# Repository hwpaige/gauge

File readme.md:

# CHT Gauge

A twin cylinder head temperature (CHT) gauge running on a Banana Pi M4 Zero, displayed on a 1.3" round SPI LCD. Designed to look like a dark-themed aircraft avionics instrument — two filled-arc gauges side by side, one per cylinder, with colour-coded temperature zones and a D-DIN digital readout.

---

## Hardware

| Component | Part |
|---|---|
| SBC | Banana Pi M4 Zero (Allwinner H618, quad-core A53) |
| Display | Pimoroni 1.3" Round SPI Colour LCD (ST7789, 240×240) — PIM570 |
| Thermocouple | MAX31855 or MAX6675 breakout (×2, one per cylinder) |
| OS | Armbian Debian Trixie Minimal |

**Important**: The kernel must provide `/dev/fb0` for the ST7789 (see "Kernel framebuffer driver" below). The Python app no longer drives the display directly.

---

## Wiring

### Display → BPI M4 Zero 40-pin header

The kernel framebuffer overlay (not the Python app) owns the pins. Example mapping used by current overlays/driver code (confirm against your .dts):

| Display Pin | Signal          | BPI Header Pin | Notes (Allwinner)     |
|-------------|-----------------|----------------|-----------------------|
| VCC         | 3.3V            | Pin 1          |                       |
| GND         | GND             | Pin 6          |                       |
| CS          | SPI1 CS0 (PH5)  | Pin 24         |                       |
| SCK         | SPI1 SCLK (PH6) | Pin 23         |                       |
| MOSI        | SPI1 MOSI (PH7) | Pin 19         |                       |
| DC          | PI16            | Pin 18         | (offset 272)          |
| RST         | PC2             | Pin 22         | (offset 66)           |
| (BL)        | (backlight)     | (Pin 35)       | Tie to 3.3V (Pin 1) if not software-controlled |

> Backlight: tie BL directly to 3.3V for always-on (recommended for gauge). The kernel panel driver typically handles reset/DC in its DT.

### Thermocouple (MAX31855 / MAX6675) — to be wired

Thermocouples share the SPI bus with the display using separate CS pins. Wiring and sensor code will be added in a future update.

---

## Project Structure

```
cht-gauge/
├── setup.sh          # One-shot bootstrap — run on fresh Armbian flash
├── gauge.py          # Main application (uses kernel /dev/fb0)
├── run.sh            # Launch script
├── test_display.py   # Legacy userspace test (may fail once kernel owns display)
├── pin_test.py       # Dev tool for probing GPIOs/SPI (kernel pins will be busy)
├── driver.py         # Legacy userspace ST7789 driver (kept for reference)
├── .gitignore
└── fonts/
    └── README.md     # Fonts are downloaded by setup.sh, not committed to repo
```

---

## Fresh Install Instructions

### 1. Flash Armbian

Download **Armbian Debian Trixie Minimal** for BPI M4 Zero:
```
https://dl.armbian.com/bananapim4zero/Trixie_current_minimal
```

Flash with [Armbian Imager](https://imager.armbian.com) or Balena Etcher. Pre-configure WiFi credentials in the imager before flashing.

### 2. SSH in

Find the device IP via your router's DHCP client list, then:

```bash
ssh root@<ip-address>
# Default password: 1234 (you'll be prompted to change it)
```

### 3. Run setup

```bash
wget https://raw.githubusercontent.com/hwpaige/gauge/master/setup.sh
bash setup.sh
```

The script will:
- Set the hostname to `moto` (SSH via `root@moto.local` after reboot)
- Enable SPI in `/boot/armbianEnv.txt`
- Install all system and Python dependencies
- Clone this repo to `/root/gauge`
- Download the D-DIN font
- Create a Python virtual environment and install packages
- Prompt to reboot

After reboot, SSH back in with:

```bash
ssh root@moto.local
```

### 4. Test the display

Once the kernel framebuffer driver is active (see below), the display is the system primary framebuffer. A basic test that the fb is working:

```bash
cat /dev/urandom > /dev/fb0   # noise on screen; Ctrl-C to stop
```

Or (inside venv):

```bash
cd /root/gauge
source venv/bin/activate
python3 -c "
import pygame, os
os.environ['SDL_VIDEODRIVER']='fbcon'; os.environ['SDL_FBDEV']='/dev/fb0'
pygame.init()
s = pygame.display.set_mode((240,280))
s.fill((255,0,0)); pygame.display.flip()
input('red fb - press enter'); pygame.quit()
"
```

(If the legacy `test_display.py` using the Python `st7789` package fails with EBUSY, that is expected once the kernel driver owns the pins — it is no longer needed.)

See "Kernel framebuffer driver" section for how the display becomes `/dev/fb0`.

### 5. Run the gauge

```bash
/root/gauge/run.sh
```

(Or manually: `cd /root/gauge && source venv/bin/activate && python3 gauge.py`)

**Important:** Because the kernel is now driving the round display as the primary framebuffer/console, you must run the gauge while on the **actual Linux console** that the display is attached to (not over SSH in most cases).

- Easiest for testing: Plug a USB keyboard into the Banana Pi. The round display should be showing the login prompt. Login directly there as root and run the command on that console.
- SSH sessions often produce `pygame.error: fbcon not available` because the SDL fbcon driver needs a real virtual terminal context.
- For production (recommended): use the included `gauge.service` so it starts automatically on boot and takes over the round display console. No keyboard or SSH run needed after setup.

### Auto-start via systemd (recommended)

From SSH on the Pi:

```bash
cd /root/gauge
git pull   # get the latest gauge.service if you haven't already

sudo cp gauge.service /etc/systemd/system/
sudo systemctl daemon-reload
sudo systemctl enable --now gauge.service

# Optional: stop the default getty so the gauge owns the console cleanly
# (the service tries to chvt to tty1)
sudo systemctl stop getty@tty1.service
sudo systemctl disable getty@tty1.service
```

Check status:

```bash
systemctl status gauge.service
journalctl -u gauge.service -f
```

To stop it temporarily and get a console back:

```bash
sudo systemctl stop gauge.service
sudo chvt 1
# or reboot
```

The service is configured to restart on failure and attaches to the framebuffer console.

See the on-screen error message in the new gauge.py for more details and a quick kernel-fb test command that *does* work over SSH.

---

## Application

`gauge.py` renders two CHT gauges using **pygame** directed at the Linux framebuffer (`/dev/fb0`) via SDL fbcon — no desktop environment required.

The kernel (via a DT overlay for the ST7789 panel, typically exposing `fb_st7789v` or equivalent) must own the display and expose `/dev/fb0` (240×280 logical with the round 240×240 visible area at y=40). The Python code now renders offscreen and writes raw RGB565 frames directly to `/dev/fb0`. This completely avoids SDL's fbcon video driver (which is frequently missing/broken in packaged SDL2 on Armbian) while still benefiting from the kernel's smooth panel handling.

The old userspace Python ST7789 + gpiod + spidev driver path has been removed from the main app (it conflicts with "Device or resource busy" once the kernel claims the pins).

### Gauge design

- **Black background** with slight blue tint
- **270° filled arc** sweep per gauge
- **Colour zones:**
  - Green — 0–60% of range (normal)
  - Amber — 60–85% (caution)
  - Red — 85–100% (danger)
- **Tick marks** — major at 0%, 50%, 100%; minor every 10%
- **Digital readout** in the arc colour at the gauge centre
- **D-DIN font** throughout — industrial/avionics aesthetic
- **Centre divider** with "CYLINDER HEAD TEMP" header

### Temperature ranges

Min/max values are set per-gauge in `gauge.py`:

```python
draw_gauge(screen, LEFT_CENTER,  cht1, 0, 300, "CYL 1", font, small_font)
draw_gauge(screen, RIGHT_CENTER, cht2, 0, 300, "CYL 2", font, small_font)
```

Change `0` and `300` to match your engine's actual operating range.

### Sensor reads

The `read_cht(channel)` function in `gauge.py` currently returns simulated sine-wave values for testing. Replace it with real MAX31855/MAX6675 SPI reads when the thermocouple hardware is wired up.

---

## Dependencies

### System packages

Installed by `setup.sh`:

- `gcc`, `build-essential` — for compiling Python C extensions
- `python3-venv`, `python3-dev`, `python3-pip`
- `git`, `wget`, `unzip`
- `avahi-daemon` — enables `.local` mDNS hostname resolution
- `libsdl2-dev`, `libsdl2-image-dev`, `libsdl2-ttf-dev` — pygame display

### Python packages (runtime)

Installed into `/root/gauge/venv`:

- `pygame` — rendering engine (fbcon targeting kernel `/dev/fb0`)

`st7789`, `pillow`, `spidev`, `gpiod`, `numpy` are also pulled in for the legacy test scripts only.

---

## Kernel framebuffer driver (required)

After the initial `setup.sh` (which only enables spidev), you must make the ST7789 the kernel's primary framebuffer (`/dev/fb0`) so that:

- The kernel owns DC, RST, and the SPI pins (your app will no longer get "Device or resource busy").
- Updates are smooth / tear-free (as you observed after the reboot that made the round display primary).

Typical steps (edit as root):

1. Create a device-tree overlay (example name `st7789-fb.dts`) in `/boot/overlay-user/` (or `/boot/dtb/overlay/` depending on Armbian version). A minimal overlay declares the spi bus + panel compatible (sitronix,st7789v or fbtft), with the correct GPIOs for your board (DC=PI16/272 on pin 18, RST=PC2/66 on pin 22, SPI1 on PH5-8), width/height, and any rotation/x/y offsets the round visible area needs (the gauge code assumes a 240×280 fb with visible content at y=40).

2. Compile it:
   ```
   armbian-add-overlay /boot/overlay-user/st7789-fb.dts
   ```
   (or `dtc -@ -I dts -O dtb -o /boot/dtb/allwinner/overlay/st7789-fb.dtbo ...` and add to user_overlays).

3. Edit `/boot/armbianEnv.txt`:
   ```
   overlays=... spi-spidev   # or remove spidev if the panel driver claims the bus exclusively
   user_overlays=st7789-fb
   # extraargs or param_ lines as required by your overlay (bus num, speed, etc.)
   ```

4. Reboot.

5. Verify:
   ```
   ls -l /dev/fb0
   fbset   # or cat /sys/class/graphics/fb0/virtual_size  (expect something like 240x280)
   ```

Once `/dev/fb0` is the round display, `python3 gauge.py` (or `run.sh`) will use it directly and be super smooth.

If you have a working overlay .dts that matches the Pimoroni 1.3" + BPI M4 Zero pinout (SPI1, offsets 272/66, y_off=40), contribute it!

The gauge code hard-codes the 240×280 / y=40 layout that the kernel driver must expose for the round 240×240 visible panel.

---

## Roadmap

- [ ] Wire and integrate MAX31855 thermocouple reads
- [ ] Add configurable temperature range and alarm thresholds
- [ ] Auto-launch gauge on boot via systemd service
- [ ] Add EGT (exhaust gas temperature) display mode

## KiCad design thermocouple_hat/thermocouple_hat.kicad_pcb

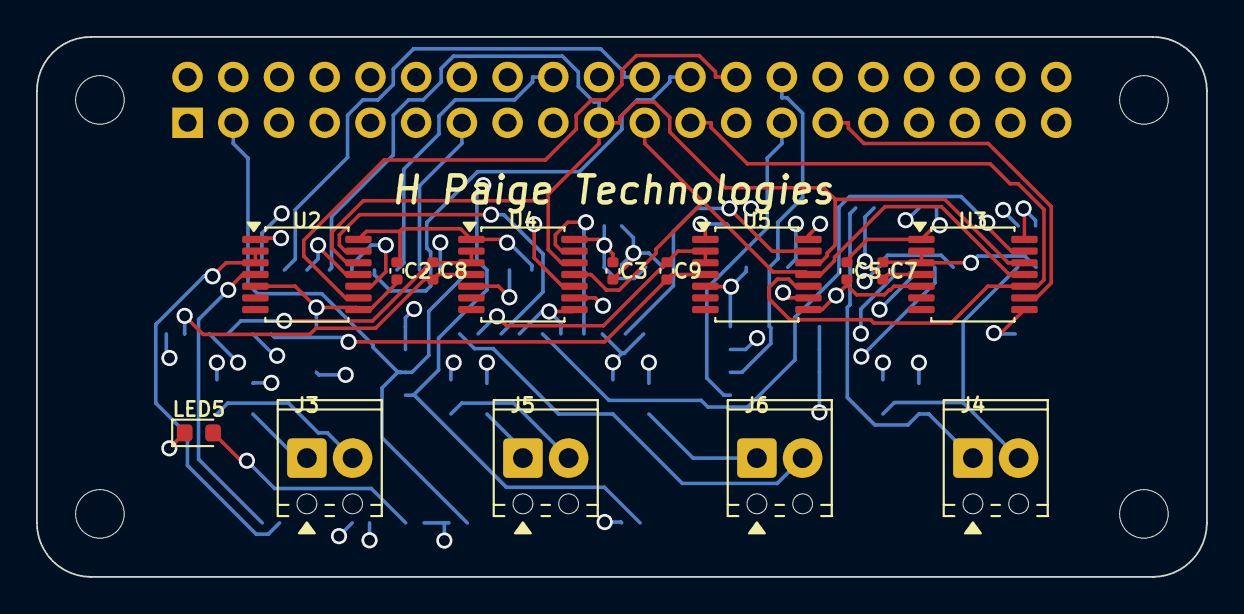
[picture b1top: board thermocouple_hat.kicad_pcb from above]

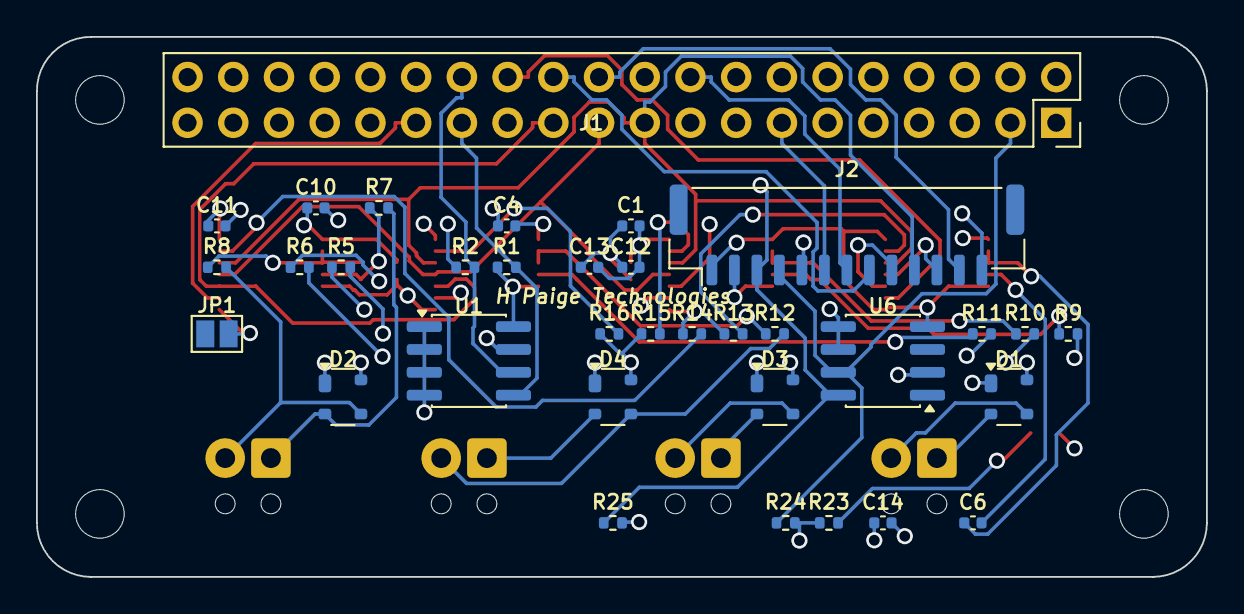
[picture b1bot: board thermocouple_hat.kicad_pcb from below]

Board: 4 copper layers, 65.0 x 30.0 mm, 53 parts (34 on the bottom side), 41 nets.

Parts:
C1, C2, C3, C4, C5, C6, C7, C8, C9, C10, C11, C12, C13, C14: 100n; C_0402_1005Metric
D1, D2, D3, D4: PRTR5V0U2X; SOT-143
J1: GPIO; PinSocket_2x20_P2.54mm_Vertical
J2: Waveshare_1.28in_Touch; JST_GH_BM13B-GHS-TBT_1x13-1MP_P1.25mm_Vertical
J3: TC1; TerminalBlock_Phoenix_MPT-0,5-2-2.54_1x02_P2.54mm_Horizontal
J4: TC2; TerminalBlock_Phoenix_MPT-0,5-2-2.54_1x02_P2.54mm_Horizontal
J5: TC3; TerminalBlock_Phoenix_MPT-0,5-2-2.54_1x02_P2.54mm_Horizontal
J6: TC4; TerminalBlock_Phoenix_MPT-0,5-2-2.54_1x02_P2.54mm_Horizontal
JP1: ID_WP; SolderJumper-2_P1.3mm_Open_Pad1.0x1.5mm
LED5: LED_GREEN; LED_0603_1608Metric
MH1, MH2, MH3, MH4: MountingHole_2.7mm_M2.5
R1, R2: 3.9k; R_0402_1005Metric
R5, R6, R7, R8, R9, R10, R11, R12: 100; R_0402_1005Metric
R13, R14, R15, R16: 10k; R_0402_1005Metric
R23: 330; R_0402_1005Metric
R24, R25: 4.7k; R_0402_1005Metric
U1: CAT24C256; SOIC-8_3.9x4.9mm_P1.27mm
U2, U3, U4, U5: MAX31856; TSSOP-14_4.4x5mm_P0.65mm
U6: DS3231MZ; SOIC-8_3.9x4.9mm_P1.27mm

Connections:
+3V3: C1.1, C2.1, C3.1, C4.1, C5.1, C10.1, C11.1, C12.1, C13.1, C14.1, D1.4, D2.4, D3.4, D4.4, J1.1, J2.2, JP1.2, R1.1, R2.1, R13.1, R14.1, R15.1, R16.1, R23.1, R24.1, R25.1, U1.8, U2.5, U2.8, U3.5, U3.8, U4.5, U4.8, U5.5, U5.8, U6.2, U6.4
+5V: J1.2, J1.4
DISP_CS: J1.24, J2.8
DISP_DC: J1.18, J2.7
DISP_RST: J1.22, J2.12
GND: C1.2, C2.2, C3.2, C4.2, C5.2, C10.2, C11.2, C12.2, C13.2, C14.2, D1.1, D2.1, D3.1, D4.1, J1.6, J1.9, J1.14, J1.20, J1.25, J1.30, J1.34, J1.39, J2.1, LED5.1, U1.1, U1.2, U1.3, U1.4, U1.7, U2.1, U2.14, U3.1, U3.14, U4.1, U4.14, U5.1, U5.14, U6.5, U6.6
GPIO17: J1.11, J2.5
GPIO26: J1.37, J2.13
GPIO27: J1.13, J2.6
ID_SCL: J1.28, R2.2, U1.6
ID_SDA: J1.27, R1.2, U1.5
PWR_LED_A: LED5.2, R23.2
SCL1: J1.5, J2.3, R25.2, U6.8
SDA1: J1.3, J2.4, R24.2, U6.7
SPI1_MISO: J1.21, J2.11, U2.11, U3.11, U4.11, U5.11
SPI1_MOSI: J1.19, J2.10, U2.12, U3.12, U4.12, U5.12
SPI1_SCK: J1.23, J2.9, U2.10, U3.10, U4.10, U5.10
TC1_CS: J1.26, U2.9
TC1_FAULT_N: R13.2, U2.13
TC1_FT_N: C6.2, R6.1, U2.2, U2.3
TC1_FT_P: C6.1, R5.1, U2.4
TC1_TMINUS: D1.3, J3.2, R6.2
TC1_TPLUS: D1.2, J3.1, R5.2
TC2_CS: J1.29, U3.9
TC2_FAULT_N: R14.2, U3.13
TC2_FT_N: C7.2, R8.1, U3.2, U3.3
TC2_FT_P: C7.1, R7.1, U3.4
TC2_TMINUS: D2.3, J4.2, R8.2
TC2_TPLUS: D2.2, J4.1, R7.2
TC3_CS: J1.31, U4.9
TC3_FAULT_N: R15.2, U4.13
TC3_FT_N: C8.2, R10.1, U4.2, U4.3
TC3_FT_P: C8.1, R9.1, U4.4
TC3_TMINUS: D3.3, J5.2, R10.2
TC3_TPLUS: D3.2, J5.1, R9.2
TC4_CS: J1.32, U5.9
TC4_FAULT_N: R16.2, U5.13
TC4_FT_N: C9.2, R12.1, U5.2, U5.3
TC4_FT_P: C9.1, R11.1, U5.4
TC4_TMINUS: D4.3, J6.2, R12.2
TC4_TPLUS: D4.2, J6.1, R11.2

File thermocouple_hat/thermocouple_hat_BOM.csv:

Designator,Comment,Footprint,Qty
"C1,C2,C3,C4,C5,C6,C7,C8,C9,C10,C11,C12,C13,C14",100n,Capacitor_SMD:C_0402_1005Metric,14
"D1,D2,D3,D4",PRTR5V0U2X,Package_TO_SOT_SMD:SOT-143,4
J1,GPIO,Connector_PinSocket_2.54mm:PinSocket_2x20_P2.54mm_Vertical,1
J2,Waveshare_1.28in_Touch,Connector_JST:JST_GH_BM13B-GHS-TBT_1x13-1MP_P1.25mm_Vertical,1
J3,TC1,"TerminalBlock_Phoenix:TerminalBlock_Phoenix_MPT-0,5-2-2.54_1x02_P2.54mm_Horizontal",1
J4,TC2,"TerminalBlock_Phoenix:TerminalBlock_Phoenix_MPT-0,5-2-2.54_1x02_P2.54mm_Horizontal",1
J5,TC3,"TerminalBlock_Phoenix:TerminalBlock_Phoenix_MPT-0,5-2-2.54_1x02_P2.54mm_Horizontal",1
J6,TC4,"TerminalBlock_Phoenix:TerminalBlock_Phoenix_MPT-0,5-2-2.54_1x02_P2.54mm_Horizontal",1
LED5,LED_GREEN,LED_SMD:LED_0603_1608Metric,1
"R1,R2",3.9k,Resistor_SMD:R_0402_1005Metric,2
"R3,R4,R17,R18",100k,Resistor_SMD:R_0402_1005Metric,4
"R5,R6,R7,R8,R9,R10,R11,R12",100,Resistor_SMD:R_0402_1005Metric,8
"R13,R14,R15,R16",10k,Resistor_SMD:R_0402_1005Metric,4
R23,330,Resistor_SMD:R_0402_1005Metric,1
"R24,R25",4.7k,Resistor_SMD:R_0402_1005Metric,2
U1,CAT24C256,Package_SO:SOIC-8_3.9x4.9mm_P1.27mm,1
"U2,U3,U4,U5",MAX31856,Package_SO:TSSOP-14_4.4x5mm_P0.65mm,4
U6,DS3231MZ,Package_SO:SOIC-8_3.9x4.9mm_P1.27mm,1

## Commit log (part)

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2026-06-13 Add initial project files for CHT gauge application
    - Create .gitignore to exclude Python artifacts and OS files
    - Add font_readme.md to document font usage
    - Implement gauge.py for rendering CHT gauges using pygame
    - Create run.sh to launch the application on the SPI display
    - Add setup.sh for environment setup and dependencies installation
    - Include test_display.py for verifying SPI display functionality
2026-06-14 Refactor gauge.py and add dev_preview.py for enhanced UI simulation
2026-06-14 Improve setup.sh to remove stale directory before cloning repository
2026-06-14 Update gauge.py and run.sh for offscreen rendering to SPI display
2026-06-14 Refactor gauge.py to use ST7789 driver and update requirements.txt for dependencies
2026-06-14 Refactor driver.py to use gpiod for GPIO handling and update gauge.py for new pin assignments
2026-06-14 Refactor driver.py to dynamically find GPIO chip and update gauge.py for new pin assignments
2026-06-14 Refactor ST7789 driver in driver.py to include software CS handling and update gauge.py for new pin mapping
2026-06-14 Refactor driver.py to remove manual CS handling in SPI initialization
2026-06-15 Switch gauge.py to kernel fbcon /dev/fb0 rendering (fixes GPIO EBUSY after kernel driver claims display)
    - Use SDL fbcon + /dev/fb0 provided by fb_st7789v (or equiv)
    - Render 240x240 gauge into 240x280 fb at y-offset 40
    - No more userspace ST7789/gpiod/spidev for main app => no resource busy
    - Matches observed 'super smooth no flickering' behavior
    - Old offscreen + disp.display() path removed
2026-06-15 Docs + scripts: document kernel fb requirement, fix EBUSY root cause, update wiring/install notes, mark legacy tools
    - README now explains why kernel /dev/fb0 is mandatory for smooth operation and to avoid GPIO busy
    - setup.sh warns + notes about the extra overlay step needed
    - requirements / run.sh / test_display updated with context
    - Wiring table corrected toward actual BPI pinouts used by the drivers
2026-06-15 Add pin_test.py (dev GPIO/SPI probe tool, with kernel-owned pin warnings)
2026-06-15 Improve fbcon initialization: set SDL env vars before importing pygame, add diagnostics, and a clear user-friendly error + instructions when 'fbcon not available' happens over SSH
2026-06-15 Document the console vs SSH requirement for running the fbcon gauge
2026-06-15 Add gauge.service systemd unit for auto-start on the kernel framebuffer console at boot
2026-06-15 Add concrete systemd service installation instructions
2026-06-15 Make error handling cleaner (no traceback spam), switch service logging to journal to avoid polluting the fb with error text, improve takeover pre-commands
2026-06-15 Switch to direct /dev/fb0 raw RGB565 write (bypasses SDL fbcon entirely). Use dummy SDL driver + offscreen rendering + direct device write for reliable kernel fb output. Simplify service accordingly.
2026-06-15 Fix red-only display: byte-swap the RGB565 conversion to match the order the original ST7789 driver used (and what the kernel fb expects for this panel).
2026-06-15 Use mmap + FBIO_WAITFORVSYNC for direct fb writes. This should get much closer to the smooth kernel console behavior the user observed (vs tearing from raw write() every frame).
2026-06-15 Guarantee first frame is written before any vsync wait. Move vsync after the write so the initial paint always happens (prevents 'nothing on screen' if ioctl blocks on first call).
2026-06-15 Add immediate solid red test frame + explicit first real gauge frame write with prints. This will show on screen whether writes are reaching the panel at all, and guarantee the app is visible right a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
2026-06-15 Add CONVERSATION_CHANGES_SUMMARY.md: detailed summary of all changes, fixes, and debugging from the full troubleshooting conversation (kernel fb takeover, direct /dev/fb0 writes, service, color fixes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
2026-06-15 Minor cleanup in readme.md (doc tweak from conversation)
